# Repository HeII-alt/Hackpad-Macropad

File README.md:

# Hackpad-Macropad
I have built a Macropad for the Hackpad competition

This is the entire Macropad

The PCB

The Schematic

The top part of the case

And the bottom part of the case 

**Part List:**\
1: 9 MX-Style switches\
2: 9 through-hole 1N4148 Diodes\
3: 1 Seed XIAO RP2040\
4: 1  EC11 Rotary encoders\
5: 1 0.91 inch OLED display

This journey has been a blast learning new and important tools like KiCAD and Fusion.

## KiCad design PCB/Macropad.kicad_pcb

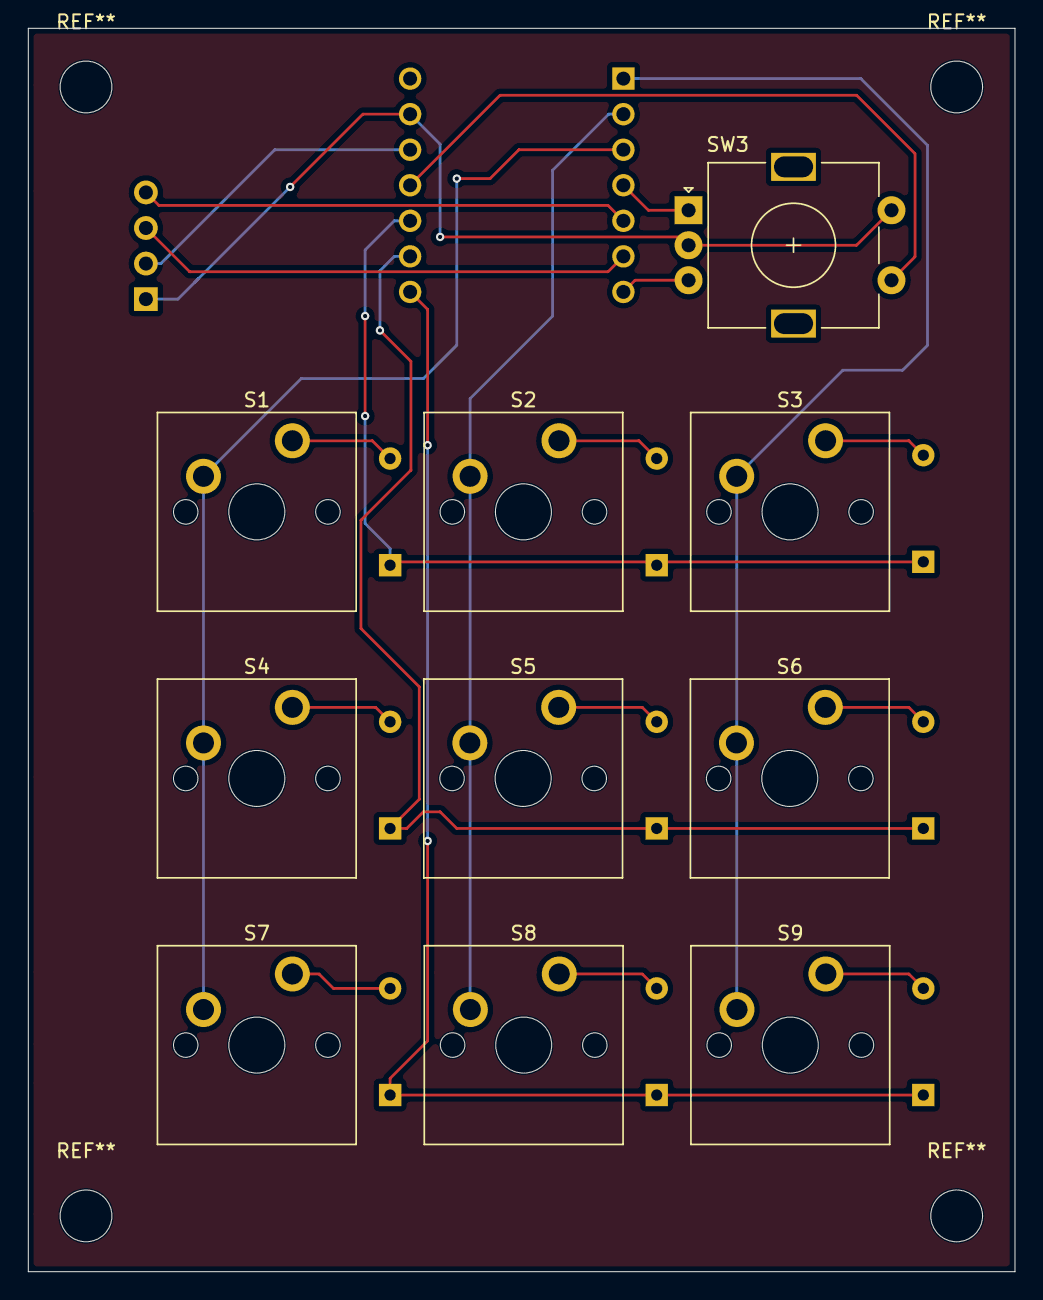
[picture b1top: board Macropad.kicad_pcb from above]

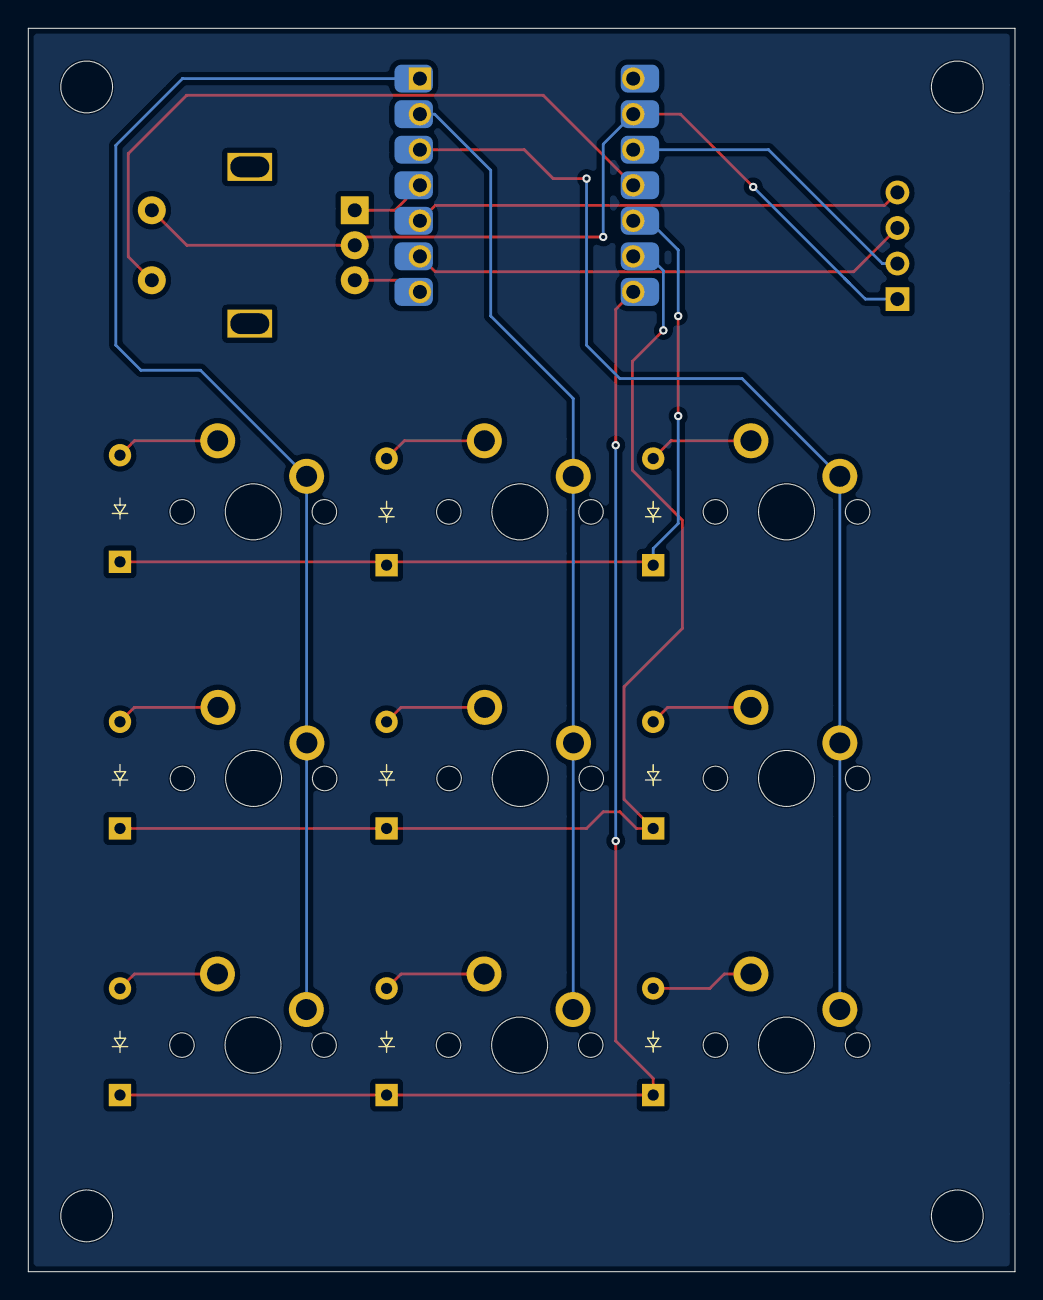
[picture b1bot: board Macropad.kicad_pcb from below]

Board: 2 copper layers, 70.5 x 88.8 mm, 21 parts (10 on the bottom side), 22 nets.

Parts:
D1, D2, D3, D4, D5, D6, D7, D8, D9: Diode_DO-35
J1: OLED_128x32
S1, S2, S3, S4, S5, S6, S7, S8, S9: MX_PCB_1.00u
SW3: RotaryEncoder_Switch_MP; RotaryEncoder_Alps_EC11E-Switch_Vertical_H20mm
U1: MCU_Seeed_XIAO_RP2040; Seeed_XIAO_RP2040

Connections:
A: SW3.A, U1.4 (PA11_A3_D3)
B: SW3.B, U1.7 (PB08_A6_D6_TX)
Collum 0: S1.1, S4.1, S7.1, U1.3 (PA10_A2_D2)
Collum 1: S2.1, S5.1, S8.1, U1.2 (PA4_A1_D1)
Collum 2: S3.1, S6.1, S9.1, U1.1 (PA02_A0_D0)
D10: SW3.S1, U1.11 (PA6_A10_D10_MOSI)
GND: J1.1 (GND), SW3.C, SW3.S2, U1.13 (GND)
unnamed: D1.2 (A), S1.2
unnamed: D2.2 (A), S2.2
unnamed: D3.2 (A), S3.2
unnamed: D4.2 (A), S4.2
unnamed: D5.2 (A), S5.2
unnamed: D6.2 (A), S6.2
unnamed: D7.2 (A), S7.2
unnamed: D8.2 (A), S8.2
unnamed: D9.2 (A), S9.2
OLED SCL: J1.3 (SCL), U1.6 (PA9_A5_D5_SCL)
OLED SDA: J1.4 (SDA), U1.5 (PA8_A4_D4_SDA)
OLED VCC: J1.2 (VCC), U1.12 (3V3)
Row 0: D1.1 (K), D2.1 (K), D3.1 (K), U1.10 (PA5_A9_D9_MISO)
Row 1: D4.1 (K), D5.1 (K), D6.1 (K), U1.9 (PA7_A8_D8_SCK)
Row 2: D7.1 (K), D8.1 (K), D9.1 (K), U1.8 (PB09_A7_D7_RX)

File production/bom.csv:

Designator,Footprint,Quantity,Value,LCSC Part #
"D1, D2, D3, D4, D5, D6, D7, D8, D9",Diode_DO-35,9,~,
J1,OLED_128x32,1,OLED_128x32,
"S1, S2, S3, S4, S5, S6, S7, S8, S9",MX_PCB_1.00u,9,~,
SW3,RotaryEncoder_Alps_EC11E-Switch_Vertical_H20mm,1,RotaryEncoder_Switch_MP,
U1,Seeed_XIAO_RP2040,1,MCU_Seeed_XIAO_RP2040,
